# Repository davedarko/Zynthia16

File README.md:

# Zynthia16
CMOS 4000 based 16-step sequencer

still working on REV1, since the first version was kind of cursed.

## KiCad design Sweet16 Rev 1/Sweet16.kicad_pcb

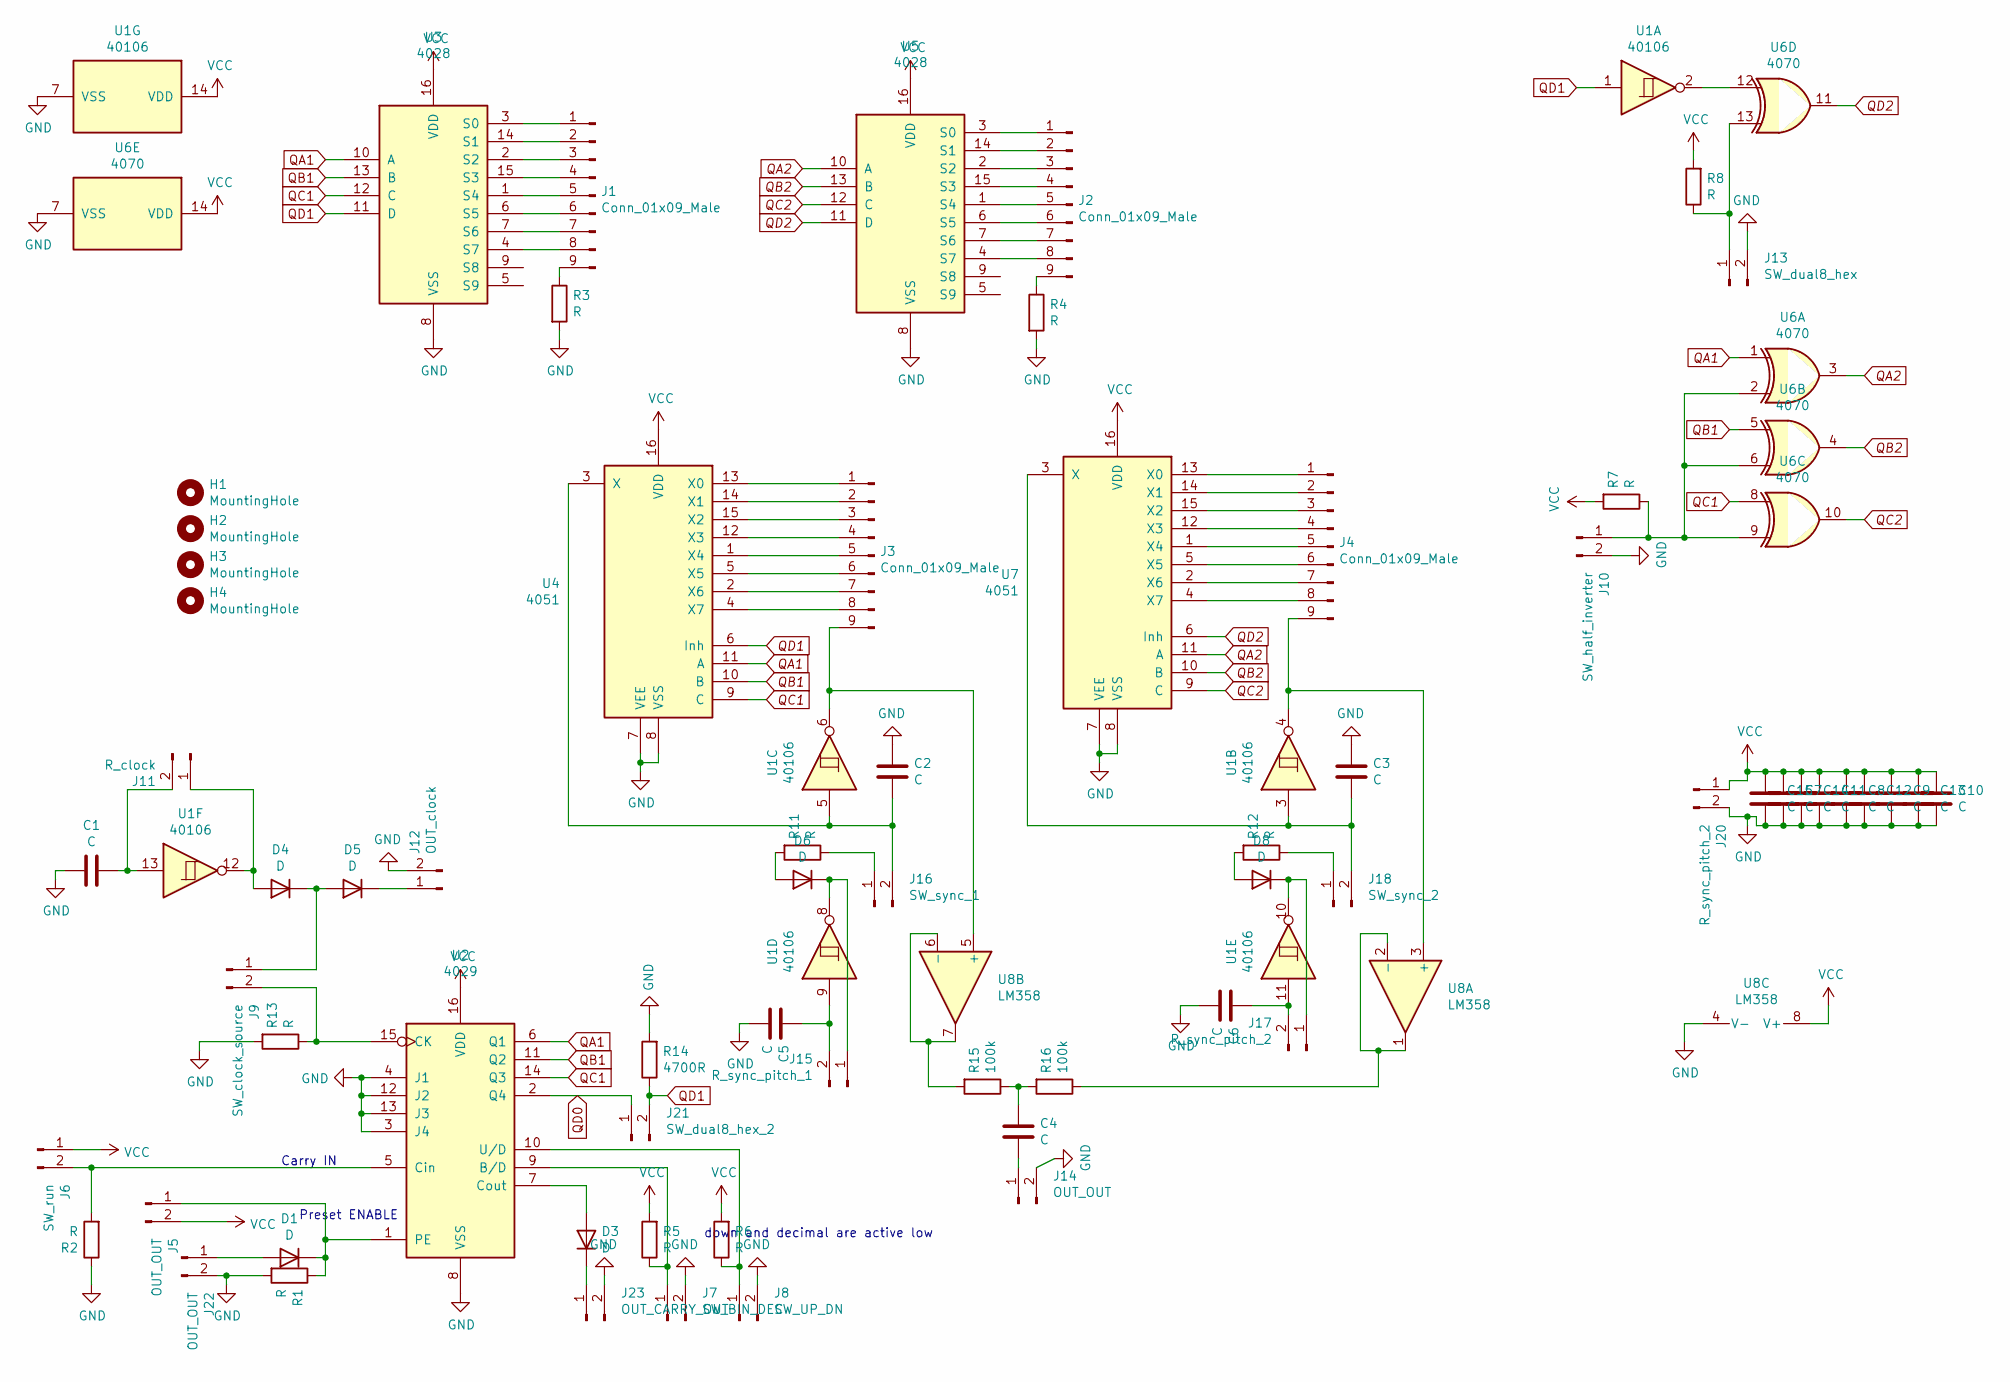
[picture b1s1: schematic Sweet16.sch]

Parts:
C1, C2, C3, C4, C5, C6, C7, C8, C9, C10, C11, C12, C13, C14, C15: C; C_Disc_D6.0mm_W2.5mm_P5.00mm
D1, D3, D4, D5, D6, D8: D; D_A-405_P7.62mm_Horizontal
H1, H2, H3, H4: MountingHole; MountingHole_3.2mm_M3
J1, J2, J3, J4: Conn_01x09_Male; PinHeader_1x09_P2.54mm_Vertical
J5, J14, J22: OUT_OUT; PinHeader_1x02_P2.54mm_Vertical
J6: SW_run; PinHeader_1x02_P2.54mm_Vertical
J7: SW_BIN_DEC; PinHeader_1x02_P2.54mm_Vertical
J8: SW_UP_DN; PinHeader_1x02_P2.54mm_Vertical
J9: SW_clock_source; PinHeader_1x02_P2.54mm_Vertical
J10: SW_half_inverter; PinHeader_1x02_P2.54mm_Vertical
J11: R_clock; PinHeader_1x02_P2.54mm_Vertical
J12: OUT_clock; PinHeader_1x02_P2.54mm_Vertical
J13: SW_dual8_hex; PinHeader_1x02_P2.54mm_Vertical
J15: R_sync_pitch_1; PinHeader_1x02_P2.54mm_Vertical
J16: SW_sync_1; PinHeader_1x02_P2.54mm_Vertical
J17, J20: R_sync_pitch_2; PinHeader_1x02_P2.54mm_Vertical
J18: SW_sync_2; PinHeader_1x02_P2.54mm_Vertical
J21: SW_dual8_hex_2; PinHeader_1x02_P2.54mm_Vertical
J23: OUT_CARRY_OUT; PinHeader_1x02_P2.54mm_Vertical
R1, R2, R3, R4, R5, R6, R7, R8, R11, R12, R13: R; R_Axial_DIN0207_L6.3mm_D2.5mm_P7.62mm_Horizontal
R14: 4700R; R_Axial_DIN0207_L6.3mm_D2.5mm_P7.62mm_Horizontal
R15, R16: 100k; R_Axial_DIN0207_L6.3mm_D2.5mm_P7.62mm_Horizontal
U1: 40106; DIP-14_W7.62mm_LongPads
U2: 4029; DIP-16_W7.62mm_LongPads
U3, U5: 4028; DIP-16_W7.62mm_LongPads
U4, U7: 4051; DIP-16_W7.62mm_LongPads
U6: 4070; DIP-14_W7.62mm_LongPads
U8: LM358; DIP-8_W7.62mm_LongPads

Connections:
GND: C1.2, C2.2, C3.2, C5.1, C6.1, C7.1, C8.1, C9.1, C10.1, C11.1, C12.1, C13.1, C14.1, C15.1, J7.2, J8.2, J10.2, J12.2, J13.2, J14.2, J20.2, J22.2, J23.2, R1.2, R2.1, R3.2, R4.2, R13.2, R14.2, U1.7 (VSS), U2.3 (J4), U2.4 (J1), U2.8 (VSS), U2.12 (J2), U2.13 (J3), U3.8 (VSS), U4.7 (VEE), U4.8 (VSS), U5.8 (VSS), U6.7 (VSS), U7.7 (VEE), U7.8 (VSS), U8.4 (V-)
unnamed: C1.1, J11.2, U1.13
unnamed: C2.1, J16.2, U1.5, U4.3 (X)
unnamed: C3.1, J18.2, U1.3, U7.3 (X)
unnamed: C4.1, J14.1
unnamed: C4.2, R15.1, R16.2
unnamed: C5.2, J15.2, U1.9
unnamed: C6.2, J17.2, U1.11
unnamed: D1.1 (K), J5.1, R1.1, U2.1 (PE)
unnamed: D1.2 (A), J22.1
unnamed: D3.1 (K), J23.1
unnamed: D3.2 (A), U2.7 (Cout)
unnamed: D4.1 (K), D5.2 (A), J9.1
unnamed: D4.2 (A), J11.1, U1.12
unnamed: D5.1 (K), J12.1
unnamed: D6.1 (K), J15.1, U1.8
unnamed: D6.2 (A), R11.2
unnamed: D8.1 (K), J17.1, U1.10
unnamed: D8.2 (A), R12.2
unnamed: J1.1, U3.3 (S0)
unnamed: J1.2, U3.14 (S1)
unnamed: J1.3, U3.2 (S2)
unnamed: J1.4, U3.15 (S3)
unnamed: J1.5, U3.1 (S4)
unnamed: J1.6, U3.6 (S5)
unnamed: J1.7, U3.7 (S6)
unnamed: J1.8, U3.4 (S7)
unnamed: J1.9, R3.1
unnamed: J2.1, U5.3 (S0)
unnamed: J2.2, U5.14 (S1)
unnamed: J2.3, U5.2 (S2)
unnamed: J2.4, U5.15 (S3)
unnamed: J2.5, U5.1 (S4)
unnamed: J2.6, U5.6 (S5)
unnamed: J2.7, U5.7 (S6)
unnamed: J2.8, U5.4 (S7)
unnamed: J2.9, R4.1
unnamed: J3.1, U4.13 (X0)
unnamed: J3.2, U4.14 (X1)
unnamed: J3.3, U4.15 (X2)
unnamed: J3.4, U4.12 (X3)
unnamed: J3.5, U4.1 (X4)
unnamed: J3.6, U4.5 (X5)
unnamed: J3.7, U4.2 (X6)
unnamed: J3.8, U4.4 (X7)
unnamed: J3.9, U1.6, U8.5 (+)
unnamed: J4.1, U7.13 (X0)
unnamed: J4.2, U7.14 (X1)
unnamed: J4.3, U7.15 (X2)
unnamed: J4.4, U7.12 (X3)
unnamed: J4.5, U7.1 (X4)
unnamed: J4.6, U7.5 (X5)
unnamed: J4.7, U7.2 (X6)
unnamed: J4.8, U7.4 (X7)
unnamed: J4.9, U1.4, U8.3 (+)
unnamed: J6.2, R2.2, U2.5 (Cin)
unnamed: J7.1, R5.1, U2.9 (B/D)
unnamed: J8.1, R6.1, U2.10 (U/D)
unnamed: J9.2, R13.1, U2.15 (CK)
unnamed: J10.1, R7.1, U6.2, U6.6, U6.9
unnamed: J13.1, R8.1, U6.13
unnamed: J16.1, R11.1
unnamed: J18.1, R12.1
unnamed: R15.2, U8.6 (-), U8.7
unnamed: R16.1, U8.1, U8.2 (-)
unnamed: U1.2, U6.12
QA1: U2.6 (Q1), U3.10 (A), U4.11 (A), U6.1
QA2: U5.10 (A), U6.3, U7.11 (A)
QB1: U2.11 (Q2), U3.13 (B), U4.10 (B), U6.5
QB2: U5.13 (B), U6.4, U7.10 (B)
QC1: U2.14 (Q3), U3.12 (C), U4.9 (C), U6.8
QC2: U5.12 (C), U6.10, U7.9 (C)
QD0: J21.1, U2.2 (Q4)
QD1: J21.2, R14.1, U1.1, U3.11 (D), U4.6 (Inh)
QD2: U5.11 (D), U6.11, U7.6 (Inh)
VCC: C7.2, C8.2, C9.2, C10.2, C11.2, C12.2, C13.2, C14.2, C15.2, J5.2, J6.1, J20.1, R5.2, R6.2, R7.2, R8.2, U1.14 (VDD), U2.16 (VDD), U3.16 (VDD), U4.16 (VDD), U5.16 (VDD), U6.14 (VDD), U7.16 (VDD), U8.8 (V+)

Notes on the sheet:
down and decimal are active low
Carry IN
Preset ENABLE

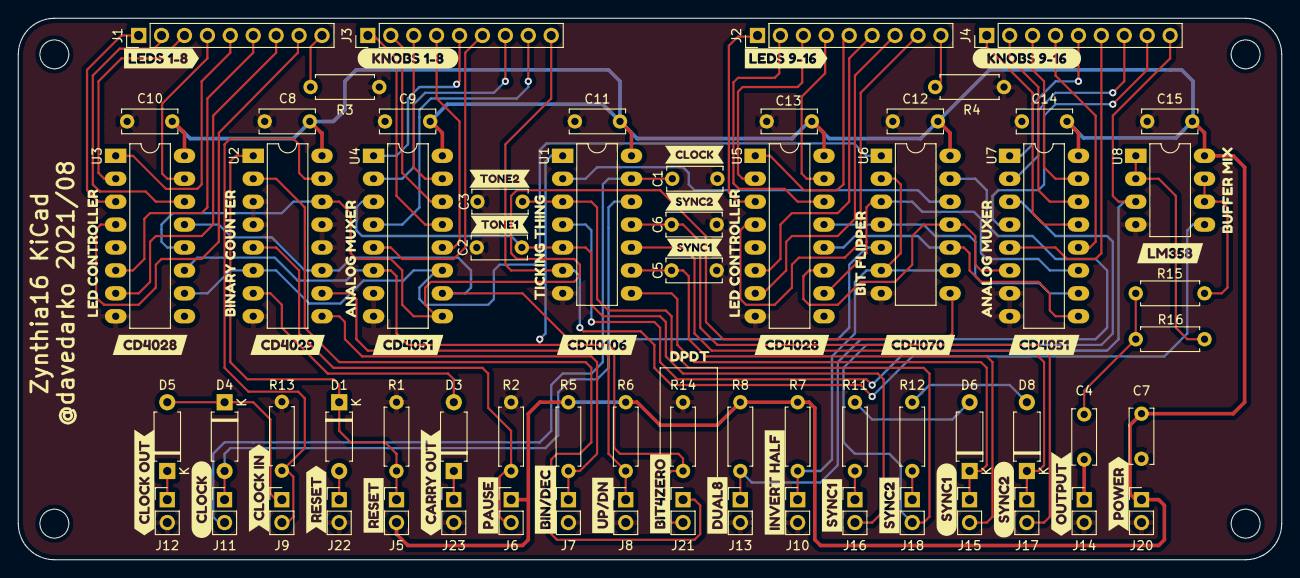
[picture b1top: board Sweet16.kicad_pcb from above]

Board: 2 copper layers, 140.0 x 60.0 mm, 113 parts (0 on the bottom side), 76 nets.

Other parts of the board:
kibuzzard-610C1A63, kibuzzard-610C1AC8, kibuzzard-610C1D73, kibuzzard-610C1E26, kibuzzard-610C23E8, kibuzzard-610C51A7, kibuzzard-610C51E0, kibuzzard-610C52EC, kibuzzard-610C55EA, kibuzzard-610C523D, kibuzzard-610C530B, kibuzzard-610C545E, kibuzzard-610C561B, kibuzzard-610C1637, kibuzzard-610C1856, kibuzzard-610C2350, kibuzzard-610C2455, kibuzzard-610C5269, kibuzzard-610C5339, kibuzzard-610C5373, kibuzzard-610C5418, kibuzzard-610C5562, kibuzzard-6111A8BD, kibuzzard-6112EA2B, kibuzzard-6112EA3D, kibuzzard-6112EA8E, kibuzzard-6112EA56, kibuzzard-6112EA78, kibuzzard-6112EAB9, kibuzzard-6112EAC9, kibuzzard-6112EADF, kibuzzard-6112EDB2, kibuzzard-6112EDD8, kibuzzard-6112EDF7, kibuzzard-6112EE9D, kibuzzard-6112EE23, kibuzzard-6112EEB7, kibuzzard-6112EED9, kibuzzard-6112EEFB, kibuzzard-6112F4A3, kibuzzard-6112F4D1, kibuzzard-6112F4F2, kibuzzard-6112F51D, kibuzzard-6112F530: G***; label

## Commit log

2021-08-05 board files and revision
2021-08-05 moved bits added labels
2021-08-06 labels
2021-08-10 48 wires to go
2021-08-10 routed, but untested
2021-08-11 laser cut case and front panel
2021-08-11 probably done
2021-09-02 inkscape planning
2021-09-15 moved the pulldown where it would work
2021-09-15 Revert "moved the pulldown where it would work"
    This reverts commit ad45cd7af2cd5e29d93eb6355ad2eb9f66b6a434.
2021-09-15 fixed pulldown AND kept all buzzard labels
